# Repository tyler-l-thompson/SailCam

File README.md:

# Description

The SailCam is an attempt to put an entirly self sufficent camera on a sail boat. The camera mounts to the stern rail of the boat and does not require an external power source. It powers itself entirely from solar energy and a battery pack.

The current design sacrifices elegance for modularity and brute force functionality. It is divided into components that can be individually detached and redesigned if needed. This allows for design iteration over a testing period. A new design will be created after core functionality is refined. 

# Video Results

All timelapse videos processed from the pictures taken by the SailCam can be found [here](https://photos.app.goo.gl/NxdoZSaHQNxRXsou5)

## Port Huron to Mackinac Race 2019
https://youtu.be/PzzFX_mOYdo

# Specifications

Battery Capacity: 33600 mAh <br>
Solar Panel Output (Per panel): 4V 400mA <br>
Image Capture Interval: 20 seconds <br>
Storage Capacity: up to 32 GB <br>

# Parts
Camera Module: ArduCAM Mini 5MP Plus OV5642 <br>
CPU: Arduino Mini Pro ATMega328 16MHz 3.3V <br>
SD Card Module: LC Studio SPI SD Card Socket Reader/Writer <br>
Real Time Clock: DS3231 <br>
Power Controller: TP4056 <br>
Batteries: 14500 3.7V 2800mAH Lithium Li-ion

# Build
## Main Board
Front of the main board without the SD card module attached<br>

Back of the main board<br>

Side view<br>

## Final Construction
Final Construction for the 2019 Mackinac Race. A lot of the chassis was 3D printed. Originally the camera module was designed to be in potrait mode, but after testing, it was changed to landscape.
<br>

<br>
<br>
<br>

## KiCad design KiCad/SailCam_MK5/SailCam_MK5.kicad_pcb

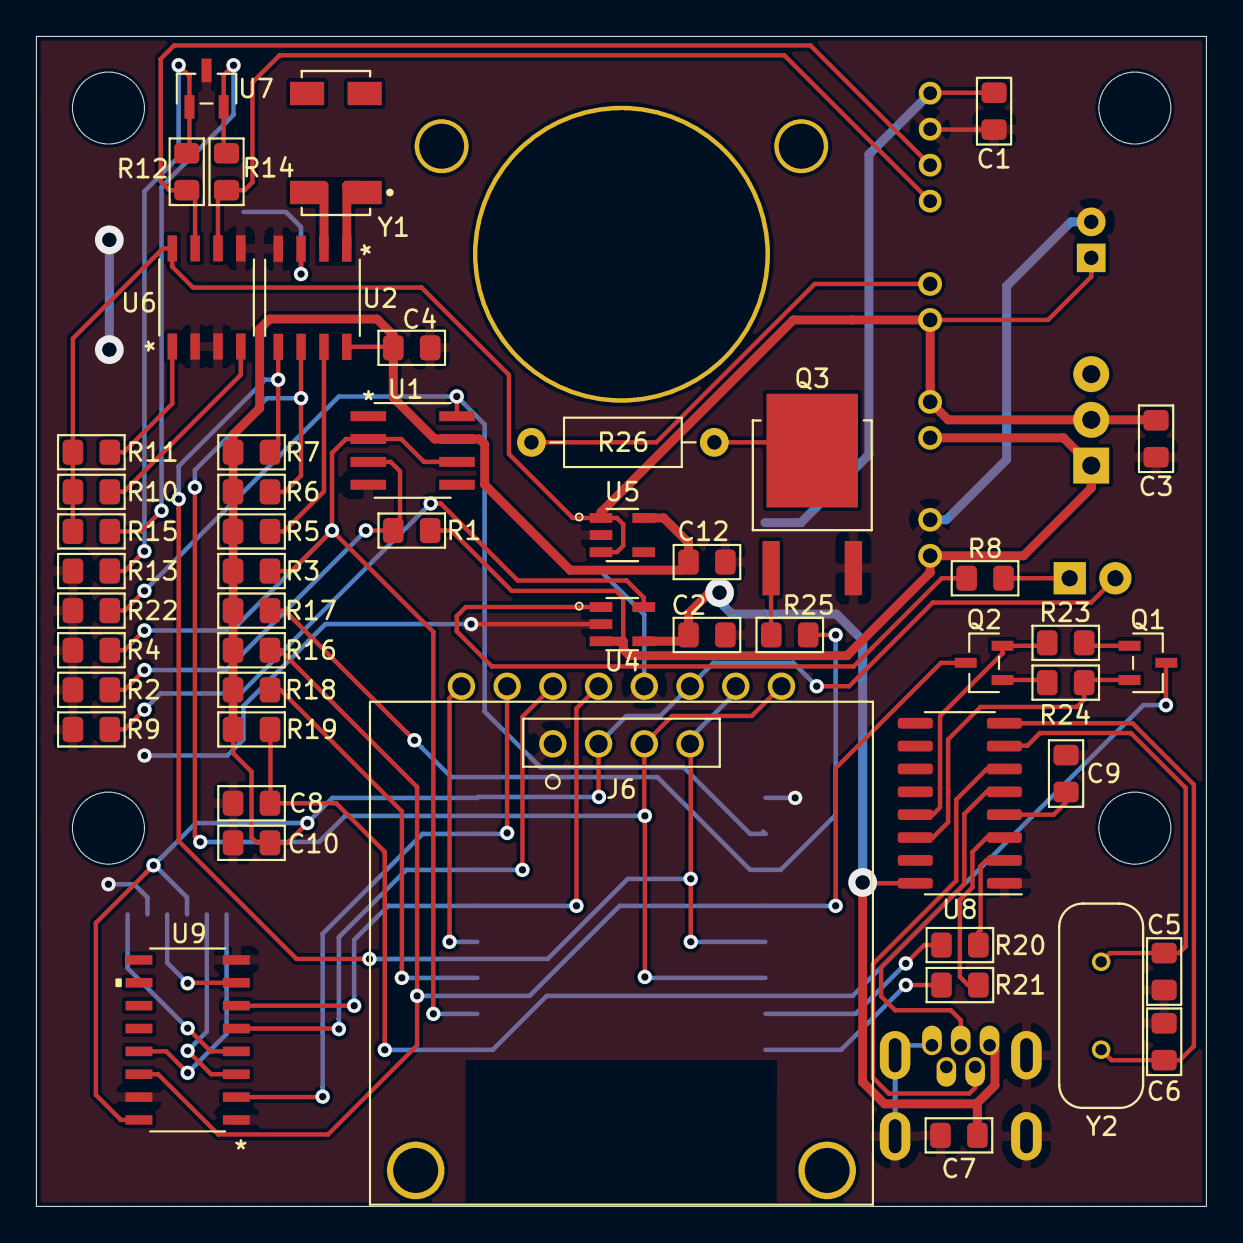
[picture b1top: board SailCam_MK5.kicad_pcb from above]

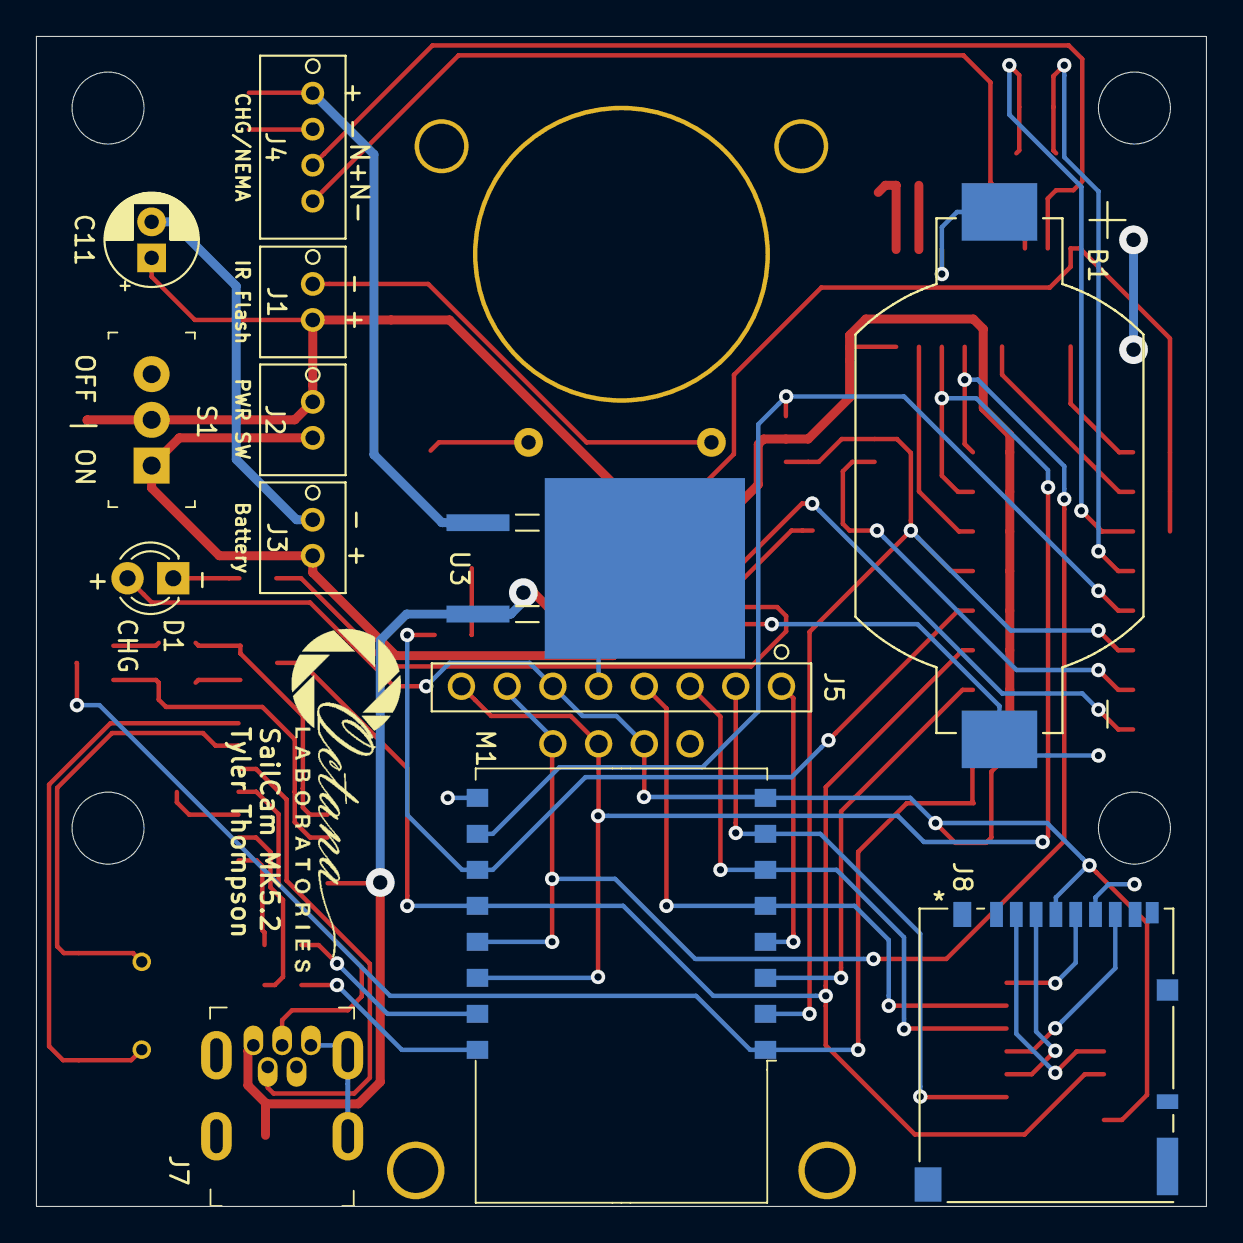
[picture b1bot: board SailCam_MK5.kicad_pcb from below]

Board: 2 copper layers, 65.0 x 65.0 mm, 64 parts (13 on the bottom side), 52 nets.

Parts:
B1: BU2032SM-BT-GTR; BAT_BU2032SM-BT-GTR
C1: 0.33 uF; C_0805_2012Metric_Pad1.15x1.40mm_HandSolder_FullSilk
C2: 1 uF; C_0805_2012Metric_Pad1.15x1.40mm_HandSolder_FullSilk
C3, C4: 10 uF; C_0805_2012Metric_Pad1.15x1.40mm_HandSolder_FullSilk
C5, C6: 22 pF; C_0805_2012Metric_Pad1.15x1.40mm_HandSolder_FullSilk
C7, C8, C9, C10, C12: 0.1 uF; C_0805_2012Metric_Pad1.15x1.40mm_HandSolder_FullSilk
C11: 100 uF; CP_Radial_D5.0mm_P2.00mm
D1: LED; LED_D3.0mm
J1, J2, J3: B2B-PH-K-SLFSN
J4: B4B-PH-K-SLFSN
J5: SSW-108-02-G-S
J6: SSW-104-02-G-S; SSW-104-02-G-S_OLED
J7: USB_B_Mini; USB_Mini_B_Female_548190519
J8: DM3BT-DSF-PEJS
M1: 2491; WIFI_Module_ESP8266_2491
Q1, Q2: SS8050-G
Q3: AOD1N60; TO228P1003X240-3N
R1, R3: 320 KΩ; C_0805_2012Metric_Pad1.15x1.40mm_HandSolder_FullSilk
R2, R4: 100 KΩ; C_0805_2012Metric_Pad1.15x1.40mm_HandSolder_FullSilk
R5, R6, R7, R25: 1 KΩ; C_0805_2012Metric_Pad1.15x1.40mm_HandSolder_FullSilk
R8: 1k Ω; C_0805_2012Metric_Pad1.15x1.40mm_HandSolder_FullSilk
R9: 3 KΩ; C_0805_2012Metric_Pad1.15x1.40mm_HandSolder_FullSilk
R10, R11, R16, R17, R18, R19, R22, R23, R24: 10 KΩ; C_0805_2012Metric_Pad1.15x1.40mm_HandSolder_FullSilk
R12, R14: 10 Ω; C_0805_2012Metric_Pad1.15x1.40mm_HandSolder_FullSilk
R13, R15: 330 Ω; C_0805_2012Metric_Pad1.15x1.40mm_HandSolder_FullSilk
R20, R21: 470 Ω; C_0805_2012Metric_Pad1.15x1.40mm_HandSolder_FullSilk
R26: 10 KΩ; R_Axial_DIN0207_L6.3mm_D2.5mm_P10.16mm_Horizontal
S1: SW_SPST; Switch_Toggle_ATE1D-2M3-10-Z
U1: ADA4841-1YRZ-R7
U2: DS1672S-33+T&R; DS1672S-33&plus_T&R
U3: NCV7805BD2TG
U4: LTC4054ES5-4.2#TRMPBF; SOT95P280X100-5N
U5: XC6220B331MR-G; SOT95P280X100-5N
U6: MAX485CSA+; MAX485CSA&plus_
U7: SM712.TCT
U8: CH340G; SOIC-16_3.9x9.9mm_P1.27mm
U9: MC74HC365ADG
Y1: ABS25-32.768KHZ-6-1-T; XTAL_ABS25-32.768KHZ-6-1-T
Y2: ECS-120-20-4X; XTAL_ECS-120-20-4X

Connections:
/ADC0: M1.2, R3.2, R4.2, U1.2, U1.6
/Bat_Chg_Vcc: C2.1, C7.1, J7.1, U3.3, U4.4, U8.16
/CHG: C1.1, J4.1, U3.1
/Cam_CS: J5.1, M1.4
/IR_CTL: J1.1, R26.1
/MISO: J5.3, M1.6, U9.5
/MOSI: J5.2, M1.7, U9.2
/Micro/GPIO2: M1.11, R17.2, R25.1
/Micro/RST: C8.1, M1.1, Q1.3, R19.2
/Micro/Rx0: M1.15, R20.2
/Micro/Tx0: M1.16, R21.2
/MicroSD/SD_CS: J8.2, U9.13
/MicroSD/SD_MISO: J8.7, U9.4
/MicroSD/SD_MOSI: J8.3, U9.3
/MicroSD/SD_SCK: J8.5, U9.7
/NEMA+: J4.3, R12.1, U6.7
/NEMA-: J4.4, R14.1, U6.6
/NEMA_Rx: R11.2, U6.1
/NEMA_Tx: R10.2, U6.4
/OpAmpEN: M1.10, R22.1, U1.8
/SCK: J5.4, M1.5, U9.6
/SCL: J5.8, J6.3, M1.14, R6.2, U2.6
/SDA: J5.7, J6.4, M1.13, R7.2, U2.5
/SD_CS: M1.12, Q2.3, R16.2, U9.14
/Vcc_5v: C3.2, C11.1, J1.2, J2.1, R10.1, R11.1, R15.1, S1.2, U5.1, U5.3, U6.8
/Vcc_5v_S: J2.2, J3.2, R1.1, S1.1, U4.3
GND: B1.-, C1.2, C2.2, C3.1, C4.2, C5.2, C6.2, C7.2, C8.2, C9.2, C10.2, C11.2, C12.2, J3.1, J4.2, J5.5, J6.1, J7.5, J7.SH, J8.6, M1.9, Q3.3, R2.1, R4.1, R9.1, R13.1, R22.2, U1.4, U2.4, U3.2, U4.2, U5.2, U6.2, U6.3, U6.5, U7.3, U8.1, U9.1, U9.8, U9.15
unnamed: B1.+, U2.3
unnamed: C5.1, U8.7, Y2.1
unnamed: C6.1, U8.8, Y2.2
unnamed: C9.1, U8.4
unnamed: D1.1, R8.2
unnamed: J7.2, U8.6
unnamed: J7.3, U8.5
unnamed: M1.3, R18.2
unnamed: Q1.1, R23.2
unnamed: Q1.2, R24.1, U8.14
unnamed: Q2.1, R24.2
unnamed: Q2.2, R23.1, U8.13
unnamed: Q3.1, R25.2
unnamed: Q3.4, R26.2
unnamed: R1.2, R2.2, U1.3
unnamed: R5.2, U2.7
unnamed: R8.1, U4.1
unnamed: R9.2, U4.5
unnamed: R12.2, R13.2, U7.1
unnamed: R14.2, R15.2, U7.2
unnamed: R20.1, U8.2
unnamed: R21.1, U8.3
unnamed: U2.1, Y1.1
unnamed: U2.2, Y1.4
VCC: C4.1, C10.1, C12.1, D1.2, J5.6, J6.2, J8.4, M1.8, R3.1, R5.1, R6.1, R7.1, R16.1, R17.1, R18.1, R19.1, U1.7, U2.8, U5.5, U9.16

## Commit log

2019-07-10 readme
2019-07-10 added 3d object files
2019-07-10 added current scripts and arduino firmware
2019-07-11 added arducam library
2019-07-11 camera spec sheets added
2019-07-15 Added TP4056 spec sheet
2019-07-15 Added DS3231 spec sheet
2019-07-16 Led flash setup for night mode
2019-07-16 DS3231 library added
2019-07-16 led flash refined
2019-07-16 added photos
2019-07-16 more pictures
2019-07-17 picture counter fix
2020-07-08 updates for mac 2020
2020-09-21 start of python processor
2021-01-31 updates for 2020
2021-08-21 initial upload of mk5 firmware
2021-08-21 added 3d cad for case and kicad pcb files for mk5
2021-10-13 mk5.2
2022-01-05 added mk5.2 docs
2022-03-23 camera self test working
2022-04-05 camera stream and capture working
2022-04-24 hardward bug fixes
2022-05-22 many many update
2022-07-29 post 2022 video processing
2022-08-11 case updates
2022-08-22 boat case updated
2023-04-16 firmware version 1.1
2023-04-22 camera settings update
2023-04-22 optimizations

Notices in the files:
parts and their libraries:
Copyright 2021 Accelerated Designs. All rights reserved.
